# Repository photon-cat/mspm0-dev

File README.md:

hello this is a little hardware dev board for the TI mspm0.

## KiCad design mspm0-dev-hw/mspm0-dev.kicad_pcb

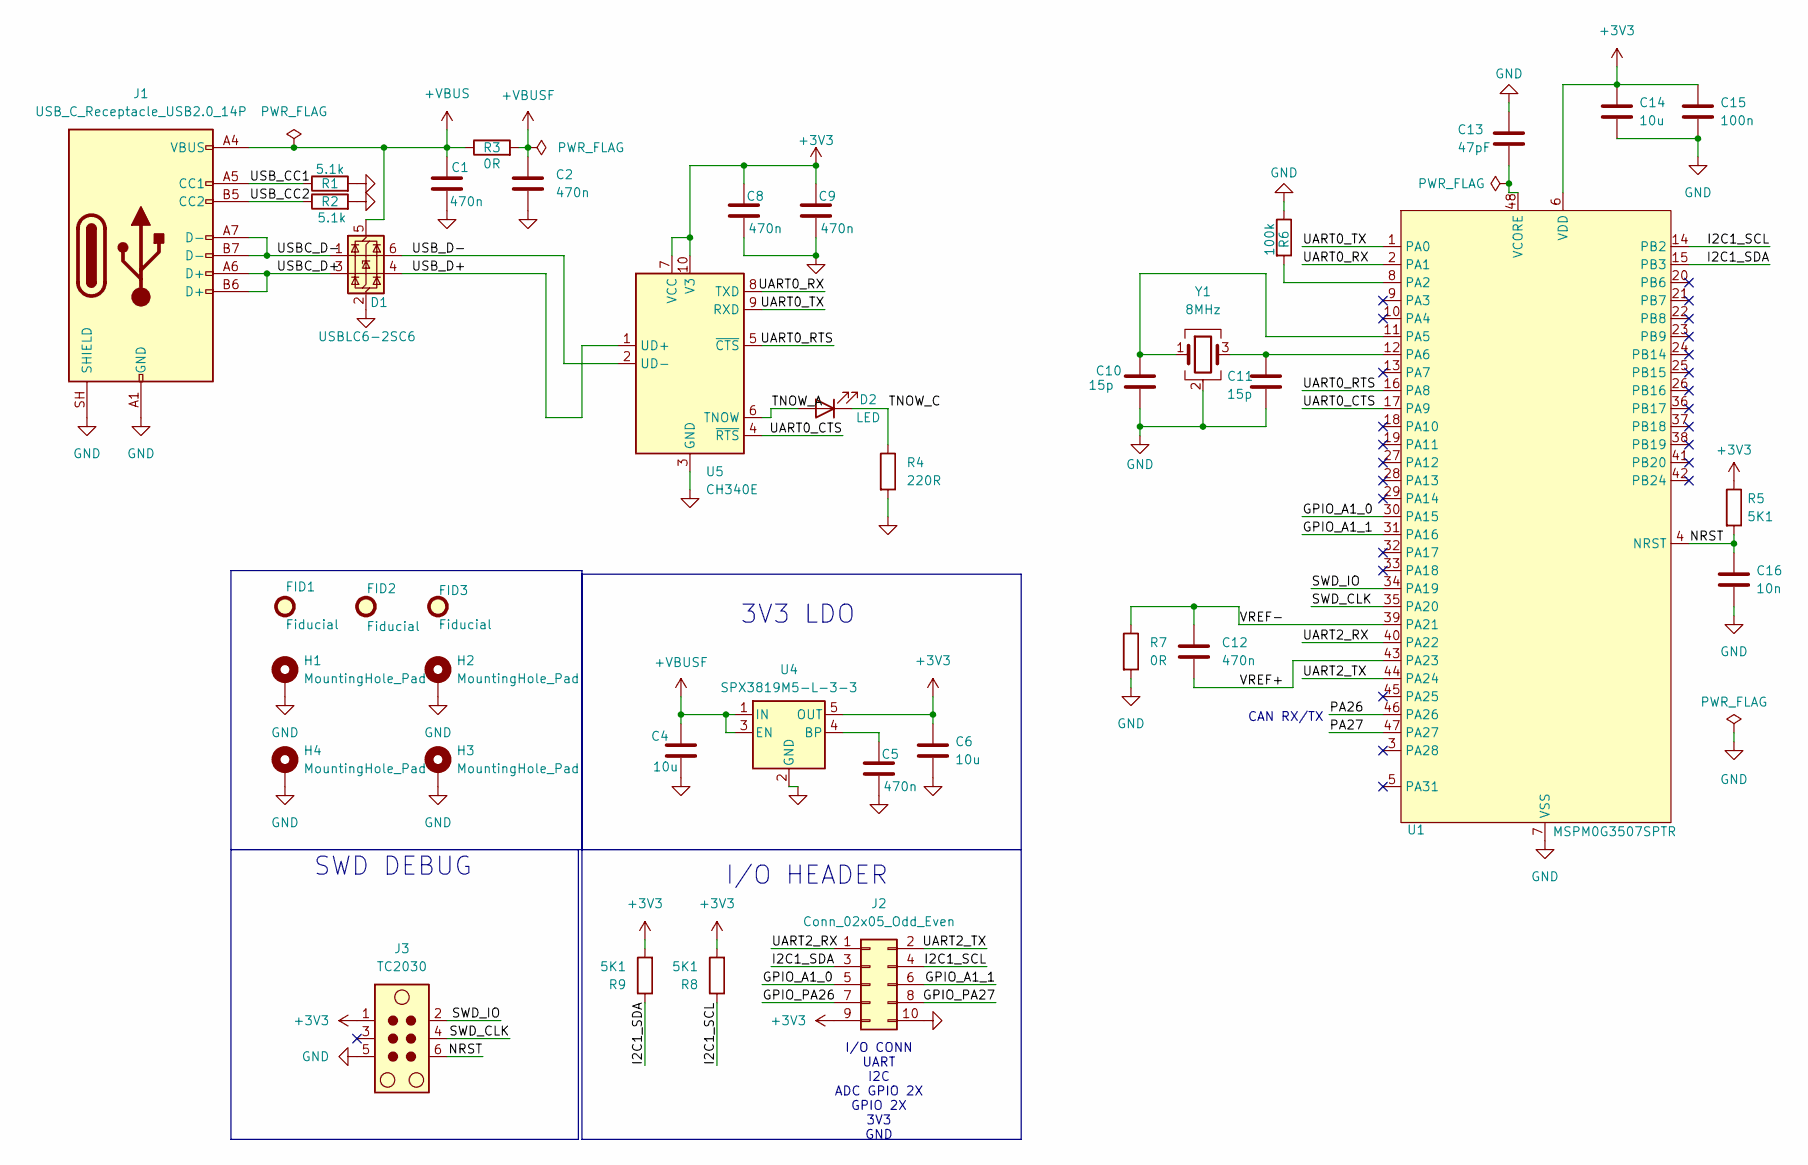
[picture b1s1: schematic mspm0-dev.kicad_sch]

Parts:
C1, C2, C5, C8, C9, C12: 470n; C_0603_1608Metric
C4, C6, C14: 10u; C_0805_2012Metric
C10, C11: 15p; C_0603_1608Metric
C13: 47pF; C_0603_1608Metric
C15: 100n; C_0603_1608Metric
C16: 10n; C_0603_1608Metric
D1: USBLC6-2SC6; SOT-23-6
D2: LED; LED_0603_1608Metric
FID1, FID2, FID3: Fiducial; Fiducial_0.5mm_Mask1mm
H1, H2, H3, H4: MountingHole_Pad; MountingHole_2.5mm_Pad_TopOnly
J1: USB_C_Receptacle_USB2.0_14P; USB_C_Receptacle_GCT_USB4110
J2: Conn_02x05_Odd_Even; PinHeader_2x05_P2.54mm_Horizontal
J3: TC2030; Tag-Connect_TC2030-IDC-NL_2x03_P1.27mm_Vertical
R1, R2: 5.1k; R_0603_1608Metric
R3, R7: 0R; R_0603_1608Metric
R4: 220R; R_0603_1608Metric
R5, R8, R9: 5K1; R_0603_1608Metric
R6: 100k; R_0603_1608Metric; Tolerence 0.1%
U1: MSPM0G3507SPTR; LQFP-48_7x7mm_P0.5mm; Manufacturer Part Number MSPM0G3507SPTR; LCSC C22362630
U4: SPX3819M5-L-3-3; SOT-23-5
U5: CH340E; MSOP-10_3x3mm_P0.5mm
Y1: 8MHz; Crystal_SMD_2520-4Pin_2.5x2.0mm

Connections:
+3V3: C6.1, C8.1, C9.1, C14.1, C15.1, J2.9, J3.1, R5.1, R8.2, R9.2, U1.6 (VDD), U4.5 (OUT), U5.7 (VCC), U5.10 (V3)
+VBUS: C1.1, D1.5 (VBUS), J1.A4 (VBUS), J1.A9 (VBUS), J1.B4 (VBUS), J1.B9 (VBUS), R3.1
+VBUSF: C2.1, C4.1, R3.2, U4.1 (IN), U4.3 (EN)
/GPIO_A1_0: J2.5, U1.30 (PA15)
/GPIO_A1_1: J2.6, U1.31 (PA16)
/GPIO_PA26: J2.7
/GPIO_PA27: J2.8
/I2C1_SCL: J2.4, R8.1, U1.14 (PB2)
/I2C1_SDA: J2.3, R9.1, U1.15 (PB3)
/NRST: C16.1, J3.6, R5.2, U1.4 (NRST)
/PA26: U1.46 (PA26)
/PA27: U1.47 (PA27)
/SWD_CLK: J3.4, U1.35 (PA20)
/SWD_IO: J3.2, U1.34 (PA19)
/TNOW_A: D2.2 (A), U5.6 (TNOW)
/TNOW_C: D2.1 (K), R4.1
/UART0_CTS: U1.17 (PA9), U5.4 (~RTS)
/UART0_RTS: U1.16 (PA8), U5.5 (~CTS)
/UART0_RX: U1.2 (PA1), U5.8 (TXD)
/UART0_TX: U1.1 (PA0), U5.9 (RXD)
/UART2_RX: J2.1, U1.40 (PA22)
/UART2_TX: J2.2, U1.44 (PA24)
/USBC_D+: D1.3 (I/O2), J1.A6 (D+), J1.B6 (D+)
/USBC_D-: D1.1 (I/O1), J1.A7 (D-), J1.B7 (D-)
/USB_CC1: J1.A5 (CC1), R1.1
/USB_CC2: J1.B5 (CC2), R2.1
/USB_D+: D1.4 (I/O2), U5.1 (UD+)
/USB_D-: D1.6 (I/O1), U5.2 (UD-)
/VREF+: C12.2, U1.43 (PA23)
/VREF-: C12.1, R7.1, U1.39 (PA21)
GND: C1.2, C2.2, C4.2, C5.2, C6.2, C8.2, C9.2, C10.2, C11.2, C13.1, C14.2, C15.2, C16.2, D1.2 (GND), H1.1 (1_1), H2.1 (1_1), H3.1 (1_1), H4.1 (1_1), J1.A1 (GND), J1.A12 (GND), J1.B1 (GND), J1.B12 (GND), J1.SH (SHIELD), J2.10, J3.5, R1.2, R2.2, R4.2, R6.1, R7.2, U1.7 (VSS), U4.2 (GND), U5.3 (GND), Y1.2 (G), Y1.4 (G)
unnamed: R6.2, U1.8 (PA2)
unnamed: C10.1, U1.11 (PA5), Y1.1
unnamed: C11.1, U1.12 (PA6), Y1.3
unnamed: C13.2, U1.48 (VCORE)
unnamed: C5.1, U4.4 (BP)

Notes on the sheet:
3V3 LDO
I/O CONN UART I2C ADC GPIO 2X GPIO 2X 3V3 GND
CAN RX/TX
SWD DEBUG
I/O HEADER

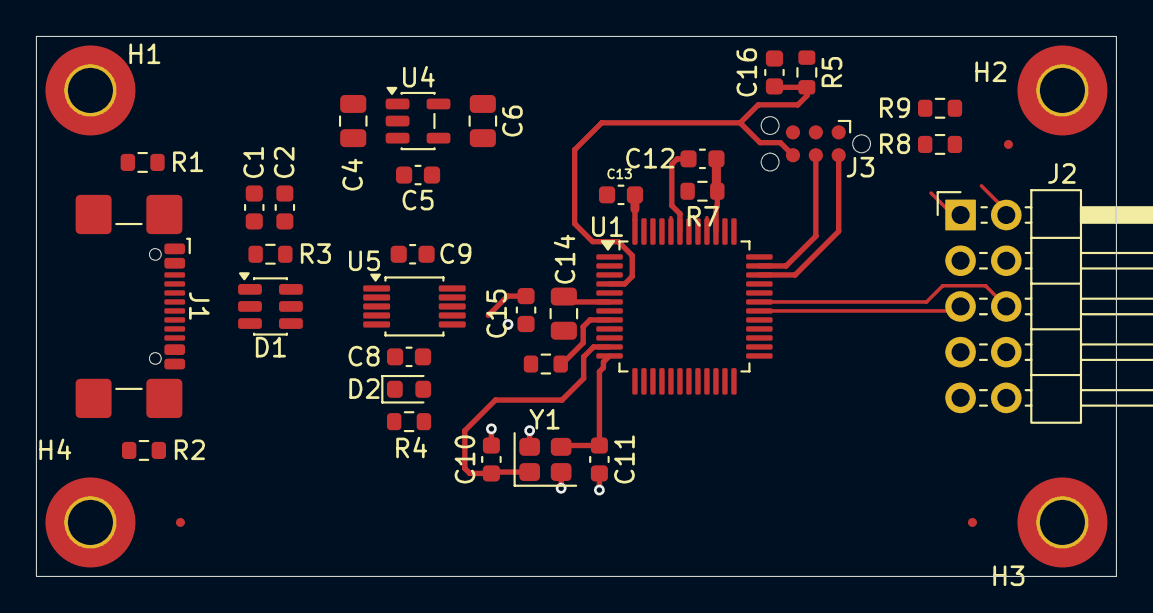
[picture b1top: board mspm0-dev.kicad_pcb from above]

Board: 2 copper layers, 60.0 x 30.0 mm, 39 parts (0 on the bottom side), 32 nets.
